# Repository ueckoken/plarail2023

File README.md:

# plarail2023

プラレールをIoT化して自動制御します

## これはなに？

このリポジトリでは電気通信大学工学研究部のプラレール企画のコードやドキュメントを管理しています。

## ドキュメント

プラレール企画に関する情報は以下のリンクにまとめます。

[https://ueckoken.github.io/plarail2023/](https://ueckoken.github.io/plarail2023/)

## コントリビュータのみなさんへ

GitHub Actions による CI/CD を走らせるために main ブランチへの直接コミットを禁止しています。 プルリクエストを発行してください。

PR の Reviewer には似たような PR で指定されている人を指定してください。内容ごとにタグを付けているので調べるときはぜひ活用ください。

PR が Approve されたら PR の Author が直接マージして下さい。

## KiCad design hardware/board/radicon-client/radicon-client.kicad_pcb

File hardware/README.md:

# hardware

ESP32などのハードウェアのコードを格納

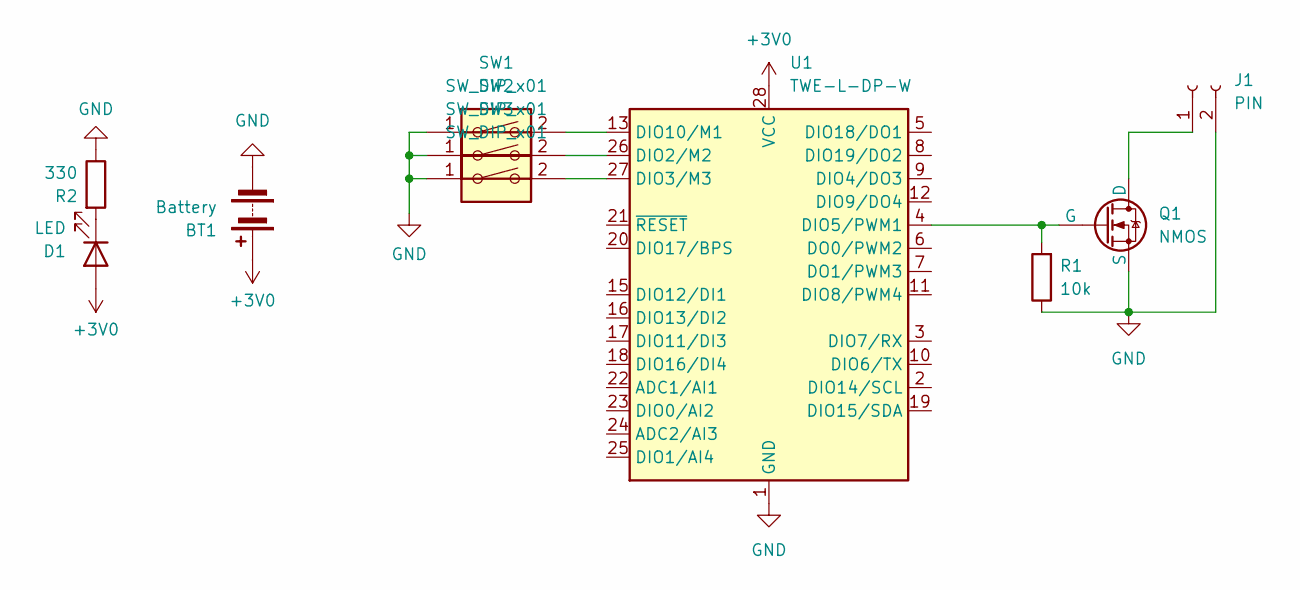
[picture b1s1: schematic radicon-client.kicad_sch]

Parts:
BT1: Battery; BatteryHolder_Keystone_103_1x20mm
D1: LED; LED_D3.0mm
J1: PIN; JST_PH_S2B-PH-K_1x02_P2.00mm_Horizontal
Q1: NMOS; TO-252-2
R1: 10k; R_Axial_DIN0207_L6.3mm_D2.5mm_P10.16mm_Horizontal
R2: 330; R_Axial_DIN0207_L6.3mm_D2.5mm_P10.16mm_Horizontal
SW1, SW2, SW3: SW_DIP_x01; SolderJumper-2_P1.3mm_Open_TrianglePad1.0x1.5mm
U1: TWE-L-DP-W; DIP-28_W15.24mm

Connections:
+3V0: BT1.1 (+), D1.2 (A), U1.28 (VCC)
GND: BT1.2 (-), J1.2, Q1.3 (S), R1.1, R2.1, SW1.1, SW2.1, SW3.1, U1.1 (GND), U1.14 (GND)
unnamed: D1.1 (K), R2.2
unnamed: J1.1, Q1.1 (D)
unnamed: Q1.2 (G), R1.2, U1.4 (DIO5/PWM1)
unnamed: SW2.2, U1.26 (DIO2/M2)
unnamed: SW3.2, U1.27 (DIO3/M3)
unnamed: SW1.2, U1.13 (DIO10/M1)

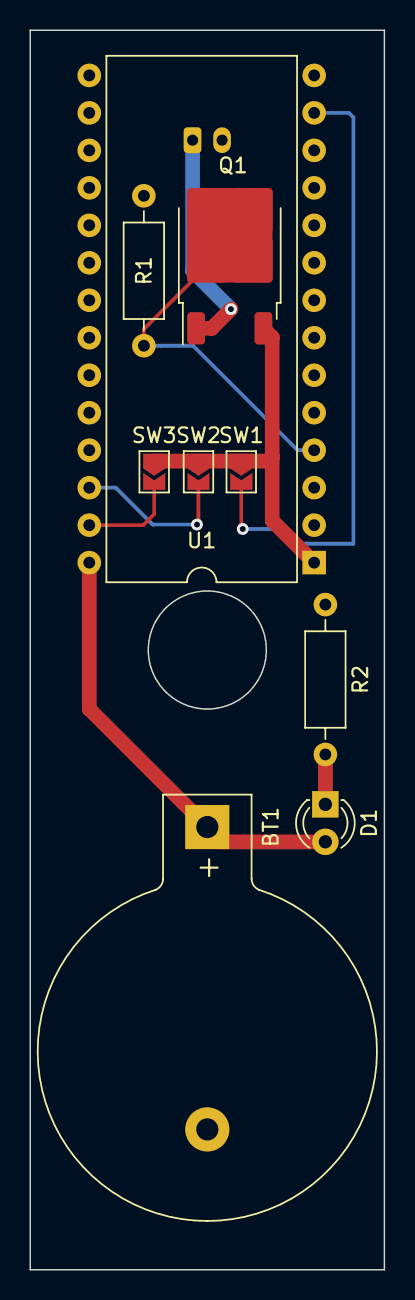
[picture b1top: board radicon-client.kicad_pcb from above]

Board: 2 copper layers, 24.0 x 84.0 mm, 10 parts (1 on the bottom side), 8 nets.

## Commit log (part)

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2023-11-19 NFCReaderとPassDetectorを追加
2023-11-19 Fix bug in login functionality
2023-11-19 Add labeler configuration for backend and hardware
2023-11-19 Update actions/cache action to v3
2023-11-19 Update actions/checkout action to v4
2023-11-19 Update actions/setup-python action to v4
2023-11-19 remove target for ci
2023-11-21 Update react monorepo
2023-11-21 http.Serverはcontextがdoneしたときにいい感じにエラーを返してくれない
2023-11-21 ioutilはDeprecated
2023-11-21 コメントを追加
2023-11-21 add typescript buf
2023-11-21 Remove ESP32 Cam UDP CI workflow
2023-11-21 DBとmqttのコネクションを使い回すようにした
2023-11-21 fix conflict
2023-11-21 Fix MQTT error and add error logging
2023-11-21 contextの名前を変える
2023-11-21 databaseがctxを受けるようにする
2023-11-21 Fix MQTT connection and error handling
2023-11-21 めっちゃマージミスっててウケる
2023-11-21 run gofmt
2023-11-21 add ts
2023-11-21 Update buf.gen.yaml and page.tsx files
2023-11-21 fix middleware load order
2023-11-21 fix called method
2023-11-21 fix loglevel
2023-11-21 fix bugs
2023-11-21 update lock
2023-11-21 add simple handler example
2023-11-21 update proto generate
2023-11-21 fix bug
2023-11-21 remove pnpm
2023-11-21 Commit from GitHub Actions (compile_PB)
2023-11-22 update proto
2023-11-22 fix proto
2023-11-22 Update Handlers
2023-11-22 add config
2023-11-22 add output
2023-11-22 fix pb
2023-11-22 udpate proto
2023-11-22 コンポーネント作成
2023-11-22 trainコンポーネントを修正
2023-11-23 add destionation
2023-11-23 Add new fields to Train struct and update dependencies
2023-11-23 remove unused ones
2023-11-23 install connect query
2023-11-23 fix typo
2023-11-23 fix path
2023-11-23 fix generation path
2023-11-23 update buf
2023-11-23 implement proxy
2023-11-23 implement views and updates of trafficlights
2023-11-23 views and updates of points
2023-11-23 fix bufbuild moromoro
2023-11-23 views and updates of trains
2023-11-24 remove import extension js
2023-11-24 CI走らせるために空コミットする
2023-11-24 fix deployment target dir
2023-11-24 pin version
2023-11-24 buildできるようにする
2023-11-24 fix import path
2023-11-24 migrate connect-ewb to connect-es
2023-11-24 backend/auto-operationをpnpmの管理下にいれる
2023-11-24 pnpmがおかしい
2023-11-24 イメージ作る
2023-11-24 キャッシュを掴まないようにする
2023-11-24 corepack enable
2023-11-24 fix nodejs version
2023-11-24 use vite
2023-11-24 auto-operationのマニフェスト書く
2023-11-24 k8sマニフェストコピペ職人
2023-11-24 kustomiza
2023-11-24 add shinjyuku.json
2023-11-24 add json files
2023-11-26 update configs
2023-11-26 add lock
2023-12-02 Update Node.js to v21
2023-12-04 Update actions/labeler action to v5
2023-12-09 Commit from GitHub Actions (compile PB)
2023-12-18 Bump golang.org/x/crypto from 0.15.0 to 0.17.0
    Bumps [golang.org/x/crypto](https://github.com/golang/crypto) from 0.15.0 to 0.17.0.
    - [Commits](https://github.com/golang/crypto/compare/v0.15.0...v0.17.0)
    ---
    updated-dependencies:
    - dependency-name: golang.org/x/crypto
    dependency-type: indirect
2024-03-14 Update module google.golang.org/protobuf to v1.33.0 [SECURITY]
2024-04-19 Update module golang.org/x/net to v0.23.0 [SECURITY]
2024-04-24 update config
2024-04-27 update for mfk
2024-04-28 update dockerfile
2024-04-28 comment out unused buttons
2024-04-28 fix error
2024-04-28 update path
2024-04-28 fux bugs
2024-04-28 update url
2024-04-28 fix url
2024-04-28 fix cors
2024-04-28 fix headers
2024-05-10 Update dependency next to v14.1.1 [SECURITY]
2024-05-12 update cors
2024-06-04 Update dependency vite to v5.0.13 [SECURITY]
2024-06-18 Update dependency ws to v8.17.1 [SECURITY]
2024-07-05 Update module github.com/rs/cors to v1.11.0 [SECURITY]
2024-09-05 Update dependency webpack to v5.94.0 [SECURITY]
2024-09-17 Update dependency next to v14.2.10 [SECURITY]
2024-10-09 Update dependency vite to v5.1.8 [SECURITY]
2025-01-21 Update dependency vite to v5.4.12 [SECURITY]
2025-06-15 ハードウェアのリコネクトを追加
2025-06-15 Add EMQX service to Docker Compose and update MQTT configuration
2025-06-15 Update dependency webpack-dev-server to v5 [SECURITY]
2025-06-15 Remove sensitive information
2025-06-15 Update Docker Compose for frontend service, enhance environment variable management, and improve styling variables in SCSS
2025-06-15 Update dependency next to v14.2.30 [SECURITY]
2025-06-15 Update module golang.org/x/net to v0.38.0 [SECURITY]
2025-06-15 Add BUILDX_BAKE_ENTITLEMENTS_FS environment variable to publish-images workflow
2025-06-15 Update Dockerfile for frontend dashboard: include package.json in dependencies copy and adjust build commands for clarity
2025-06-15 Refactor Dockerfile for frontend dashboard: remove package.json from COPY command to streamline dependency management
2025-06-15 Update Dockerfile for frontend dashboard: modify deploy command to include --legacy flag for compatibility
2025-06-15 Refactor Dockerfile for frontend dashboard: switch from distroless to nginx for serving static files and streamline build process
2025-06-18 データベース接続のクローズ処理を改善し、エラーハンドリングを強化。README.mdを追加し、State Managerの設定と起動方法を明記。
2025-06-18 GitHub Actions: Update image tagging logic for main and deployment branches
2025-06-18 レイアウトを修正
2025-06-18 Kubernetesマニフェストを追加し、各サービスのデプロイメント、サービス、PVCを定義。ローカル開発用のビルドおよびデプロイスクリプトを整備。
2025-06-19 各サービスのデプロイメントで使用するイメージをghcr.ioに変更し、imagePullPolicyをAlwaysに設定
2025-06-19 GitHub Actions: Update image tagging logic to include latest tag for main branch and deployment
2025-06-20 Kubernetes: Add seed-data job and related configurations; update deployment images and kustomization
2025-06-20 Seed Data実行スクリプトを追加し、環境に応じた設定とJobの管理機能を実装
2025-06-20 Seed data import script: Enhance logging for stop, point, and block additions; update seed-data.sh for simplified usage and remove unnecessary environment handling
2025-06-20 MapView: Update block IDs in onClick handlers for Rail components to ensure correct state mutation
2025-06-20 Remove obsolete Flux and Cert-Manager manifests
    - Deleted Flux GitRepository and Kustomization manifests for the flux-system.
    - Removed Cert-Manager Certificate, ClusterIssuer, and related Kustomization and Namespace manifests.
    - Eliminated HelmRelease and HelmRepository manifests for Cert-Manager, Kubernetes Reflector, Dashboard, and Dex.
    - Cleaned up Kustomization files that referenced the deleted resources.
2025-06-20 update ui
2025-06-20 MapView: Refactor layout with CSS modules for improved styling; update image tag in kustomization.yaml
2025-06-20 Nginx Ingress: Add installation script and update deploy script to check for nginx-ingress-controller
2025-06-20 Bump github.com/go-chi/chi/v5 from 5.0.10 to 5.2.2
    ---
    updated-dependencies:
    - dependency-name: github.com/go-chi/chi/v5
    dependency-version: 5.2.2
    dependency-type: direct:production
    ...
2025-06-20 MapEditer: Implement block state management and UI for state changes
2025-06-20 MapEditer: Display component names in the station list for better clarity
2025-06-20 kustomization.yaml: Update image tag for plarail2023-dashboard
2025-06-20 Update module github.com/go-chi/chi/v5 to v5.2.2 [SECURITY]
2025-06-21 Fix stop block mappings for ninini and nanana stations
2025-06-21 kustomization.yaml: Add new image tag for plarail2023-autooperation
2025-06-21 Fix block mappings for ninini and nanana stations; update image tag for autooperation
2025-06-21 update block
2025-06-21 Update dependency vite to v5.4.19 [SECURITY]
2025-06-21 update algorithm
2025-06-23 platformio.ini: Add missing newline; kustomization.yaml: Update image tags for dashboard and autooperation
